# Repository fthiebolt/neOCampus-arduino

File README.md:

# neOCampus-arduino | home of the neOSensor end-devices #
________________________________________________________________
# WE MOVED #
# to https://gitlab.irit.fr/gis-neocampus/neosensor/neOCampus-arduino #
________________________________________________________________

This repository provides support for the following neOCampus boards:
  * neOSensor boards based on ESP32
  * neOSensor-AirQuality board (ESP32) from CNRS' LCC lab.
  * neOSensor boards based on ESP8266 (rev. >= V2)

All this work was undertaken at Université Toulouse 3 / IRIT laboratory in the context of the [neOCampus](https://neocampus.org "neOCampus corporate") operation.

## neOSensor boards ##
neOSensor first boards releases were based on esp8266. Nowadays, we added support for esp32 and CubeCell devices :)

We added support to our neOCampus IoT management infrastructure named [sensOCampus](https://neocampus.univ-tlse3.fr "neOCampus's Wiki Home") to enable a central configuration for all of our neOSensor boards; these boards will then be able to publish their data to our infrastructure and to have those data stored in our databases.

### neOSensor-AirQuality board ###
This board comes from CNRS LCC lab, it's a PhD work undertaken by Aymen Sendi (aymen.sendi@laas.fr).
The board features four specific sensors able to measure NO2, CO, CH20, NO2 alternate.

## Getting started ##
First of all, you ought to install esp32, esp8266 or CubeCell support in your Arduino IDE (IDE version <2).

| Device   | Release   | Arduino Board Manager json file                                                                            |
|----------|-----------|------------------------------------------------------------------------------------------------------------|
| esp8266  | 3.1.2     | https://arduino.esp8266.com/stable/package_esp8266com_index.json                                           |
| esp32    | 2.0.11    | https://raw.githubusercontent.com/espressif/arduino-esp32/gh-pages/package_esp32_index.json                |
| CubeCell | *latest*  | https://github.com/HelTecAutomation/CubeCell-Arduino/releases/download/V1.3.0/package_CubeCell_index.json  |
| stm32    | *latest*  | https://github.com/stm32duino/BoardManagerFiles/raw/main/package_stmicroelectronics_index.json             |

Then, run script `./deploy.sh` and boards will get added to your Arduino boards list :)

If not already installed, you'll need python-serial package; thus either you install it at the system level
```
[fedora] dnf -y install python3-pyserial
[ubuntu] apt-get -y install python3-serial python-is-python3
```

Once you've launched the Arduino IDE, before compiling and uploading sketches to your board, you need to undertake the following steps:
  - @preferences --> set your Arduino sketchbook to `~/neOCampus-arduino/neosensor' ... this will lead to proper libraries
  - either select boards 'ESP32 arduino' --> 'neOSensor' or 'neOSensor-AirQuality' or select board 'ESP8266 arduino' --> 'neOSensor'
  - compile and upload :)
  - debug serial link speed 115200

### WiFi setup ###
Only for ESP based boards.

Once started, the board will provides a WiFi Access Point (AP) named: `neOSensor_xxxx` where xxxx are the MAC address last bytes.

**First time setup**\
In this case, AP will get available for 5mn for you to configure SSID along with WPA2 key.
So you'll have to search with your smartphone for this peucliar AP, and then connect. In case automatic redirection does not work, open a browser with http:192.168.4.1

**Changing WiFi setup**\
Once WiFi has been set, on each reboot, the neOSensor AP will get available for 50s in order for you to tweak some parameters ... or to change the WiFi it connects to.

**Reset whole configuration**\
To erase all of the previously set parameters (including WiFi settings), press the RST button for 10s when powering the device.

***

## Create branch | development of a new feature ##
In order to work on a new feature, best is to create a new branch that will get merged later during a *pull request*

```
git switch -C feature-xxxxx
```

For first commit:
```
git push --set-upstream origin feature-xxxxx
```

... then `./git-push.sh` on subsequent commits

## Merge branch | integration of an existing feature ##
After having successfully completed yout feature, you need to create a *pull request* to get your code integrated into the main branch:

```
git branch
git checkout master
git merge feature-xxxxx
./git-push.sh
```
https://www.w3schools.com/git/git_branch_merge.asp?remote=github

In the end, you can delete your local branch: `git branch -d feature-xxxxx`

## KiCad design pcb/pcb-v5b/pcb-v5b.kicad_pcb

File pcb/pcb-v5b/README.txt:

This directory holds the following:

- pcb-v5b.pro	--> main neOSensor board (esp32 30 pins based version) version 5B

- panelization files (4 designs in a single 100x100mm board)

To launch Kicad: #> kicad xxx.pro

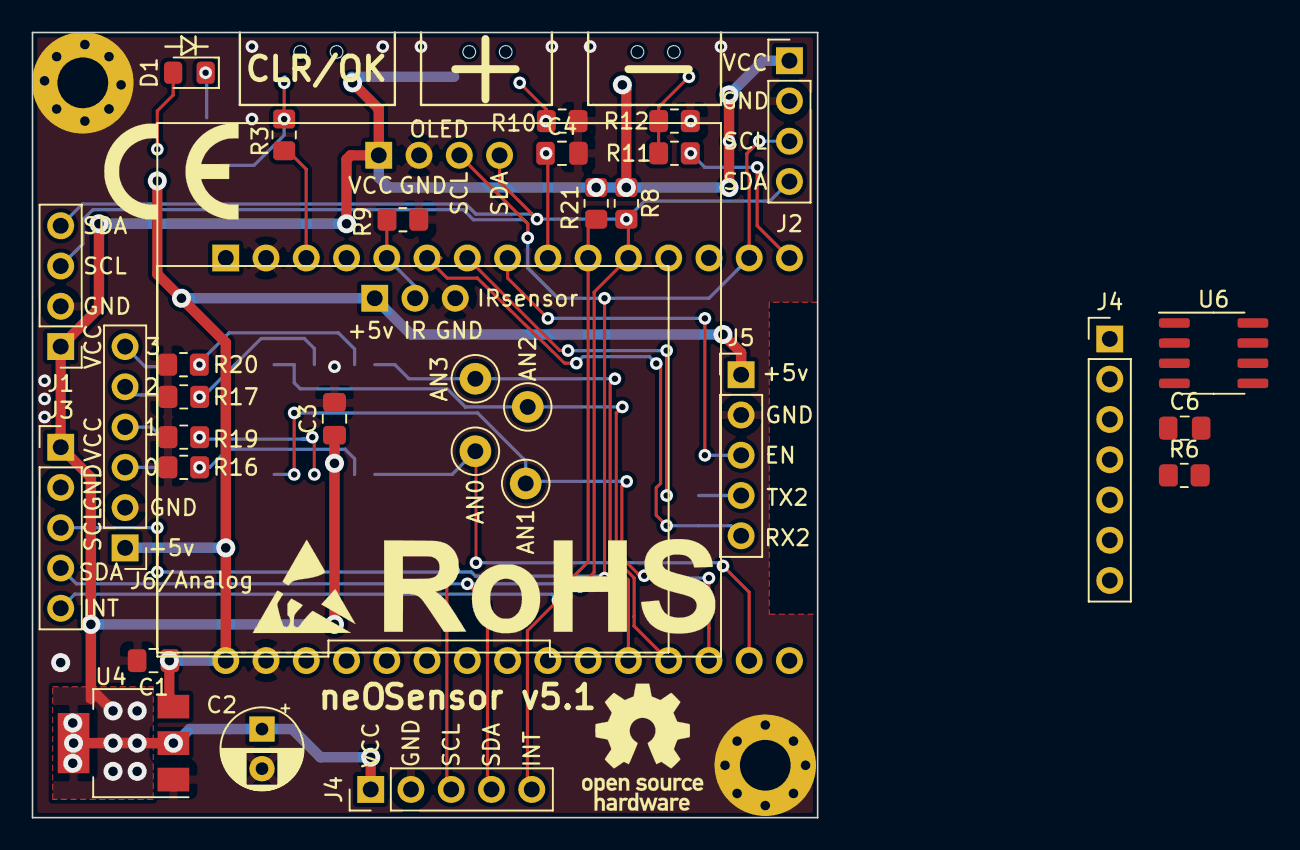
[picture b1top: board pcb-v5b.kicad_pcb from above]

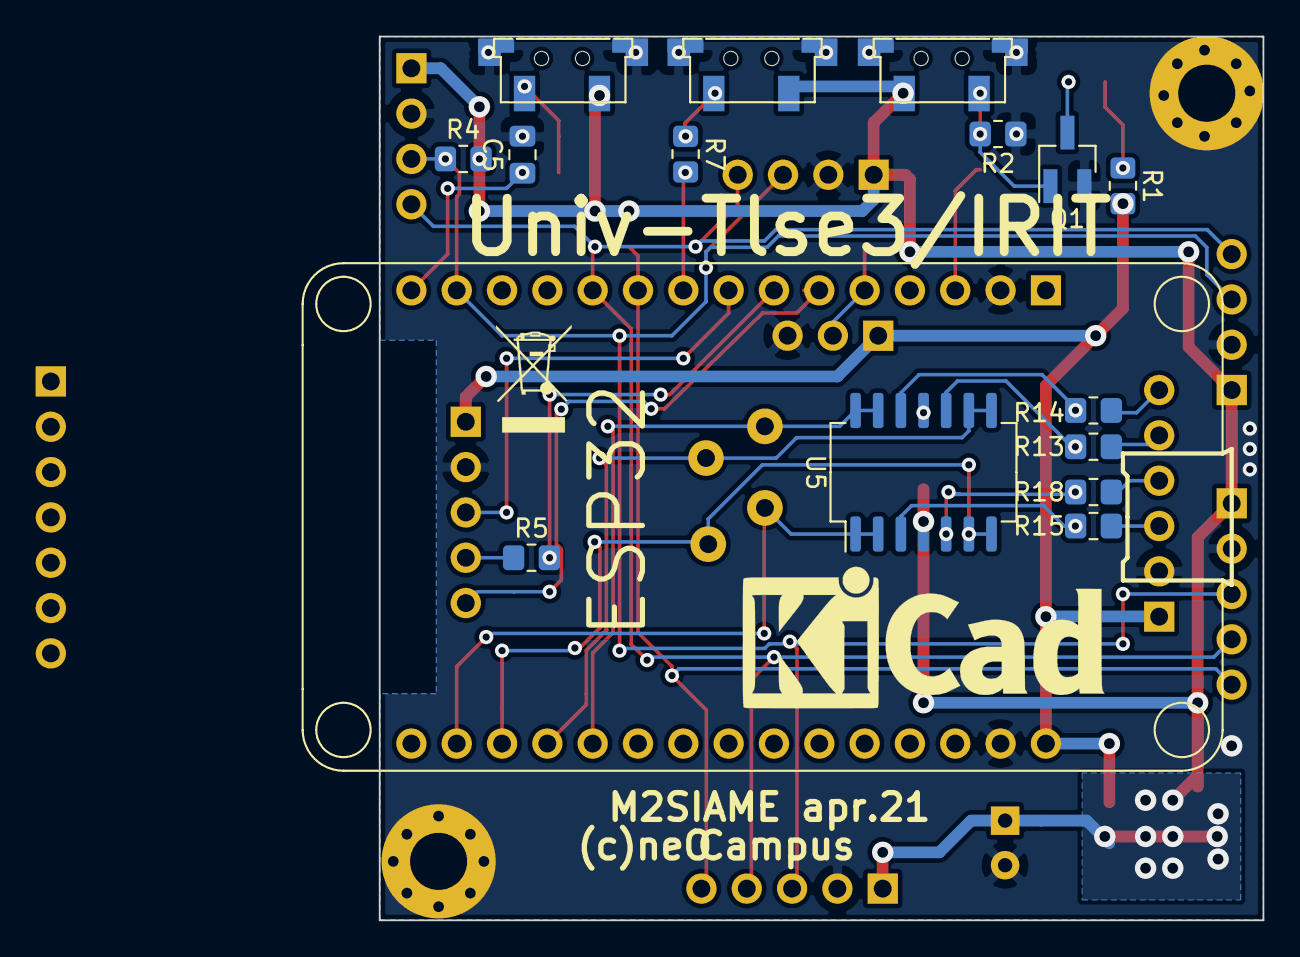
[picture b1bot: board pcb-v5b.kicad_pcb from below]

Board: 2 copper layers, 49.5 x 49.5 mm, 51 parts (16 on the bottom side), 33 nets.

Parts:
C1, C3: 100nF; C_0805_2012Metric_Pad1.18x1.45mm_HandSolder
C2: 100µF 6.3v; CP_Radial_D5.0mm_P2.50mm
C4, C5: 1uF; C_0805_2012Metric_Pad1.18x1.45mm_HandSolder
C6: 100n; C_0805_2012Metric_Pad1.18x1.45mm_HandSolder
D1: Red; LED_0805_2012Metric_Pad1.15x1.40mm_HandSolder
H1, H2: 3.2mm for MH3 screw; MountingHole_3.2mm_M3_Pad
J1, J2: Conn_01x04; PinHeader_1x04_P2.54mm_Vertical
J3, J4, J5: Conn_01x05; PinHeader_1x05_P2.54mm_Vertical
J4#2: Conn_01x07; PinHeader_1x07_P2.54mm_Vertical
J6: Conn_01x06; PinHeader_1x06_P2.54mm_Vertical
Q1: 2N7002; SOT-23_Handsoldering
R1: 150; R_0805_2012Metric_Pad1.20x1.40mm_HandSolder
R2, R7, R9, R10, R11, R12, R21: 15k; R_0805_2012Metric_Pad1.20x1.40mm_HandSolder
R3, R5, R6: 470; R_0805_2012Metric_Pad1.20x1.40mm_HandSolder
R4, R8: 4K7; R_0805_2012Metric_Pad1.20x1.40mm_HandSolder
R13, R14, R15, R18: 22k; R_0805_2012Metric_Pad1.20x1.40mm_HandSolder
R16, R17, R19, R20: 33k; R_0805_2012Metric_Pad1.20x1.40mm_HandSolder
SW1: clear; G71Y_µsw_smd
SW2: +; G71Y_µsw_smd
SW3: -; G71Y_µsw_smd
TP3: tp_an1; TestPoint_Loop_D2.50mm_Drill1.0mm
TP4: tp_an0; TestPoint_Loop_D2.50mm_Drill1.0mm
TP5: tp_an2; TestPoint_Loop_D2.50mm_Drill1.0mm
TP6: tp_an3; TestPoint_Loop_D2.50mm_Drill1.0mm
U1: HC-SR01; PIR_HC-SR01
U2: OLED1.3_I2C
U3: ESP32_dev_30p
U4: AMS1117-3.3; SOT-223-3_TabPin2
U5: LM2902; SO-14_5.3x10.2mm_P1.27mm
U6: ATECC608A-SSHDA; SOIC-8_3.9x4.9mm_P1.27mm

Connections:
+3V3: C2.1, C3.1, J1.1, J2.1, J3.1, J4.1, J4#2.3, R4.2, R8.2, R21.2, SW1.1, SW2.2, SW3.2, U2.1 (VCC), U4.2 (VO), U5.4 (V+), U6.8 (VCC)
+5V: C1.1, J5.1, J6.1, R1.2, U1.1 (V+), U3.30 (VIN), U4.3 (VI)
/ADC1_0: TP4.1, U3.17 (GPIO36), U5.1, U5.2 (-)
/ADC1_3: TP3.1, U3.18 (GPIO39), U5.6 (-), U5.7
/ADC1_6: TP5.1, U3.19 (GPIO34), U5.8, U5.9 (-)
/ADC1_7: TP6.1, U3.20 (GPIO35), U5.13 (-), U5.14
/ANA_0: J6.3, R15.1
/ANA_1: J6.4, R18.1
/ANA_2: J6.5, R13.1
/ANA_3: J6.6, R14.1
/INT: J3.5, J4.5, J4#2.7, R21.1, U3.10 (GPIO19)
/IR: R6.1, R9.2, U1.2 (OUT)
/LED: R3.1, U3.3 (GPIO15)
/PM_EN: J5.3, U3.8 (GPIO5)
/RX2: J5.5, U3.6 (GPIO16)
/SCL: J1.3, J2.3, J3.3, J4.3, J4#2.2, J4#2.5, R4.1, U2.3 (SCL), U3.14 (SCL), U6.6 (SCL)
/SDA: J1.4, J2.4, J3.4, J4.4, J4#2.1, J4#2.6, R8.1, U2.4 (SDA), U3.11 (SDA), U6.5 (SDA)
/SW2: C4.1, R7.2, U3.9 (GPIO18)
/SW3: C5.1, R11.2, U3.15 (GPIO23)
/TX2: J5.4, R5.1
GND: C1.2, C2.2, C3.2, C4.2, C5.2, C6.1, H1.1, H2.1, J1.2, J2.2, J3.2, J4.2, J4#2.4, J5.2, J6.2, Q1.2 (S), R2.1, R9.1, R10.1, R12.1, R16.1, R17.1, R19.1, R20.1, SW1.3, SW2.3, SW3.3, U1.3 (GND), U2.2 (GND), U3.2 (GND), U3.29 (GND), U4.1 (GND), U5.11 (V-), U6.4 (GND)
unnamed: D1.2 (A), R1.1
unnamed: D1.1 (K), Q1.3 (D)
unnamed: Q1.1 (G), R2.2, R3.2, SW1.2
unnamed: R7.1, R10.2, SW2.1
unnamed: R11.1, R12.2, SW3.1
unnamed: C6.2, U3.16 (EN)
unnamed: R6.2, U3.5 (GPIO4)
unnamed: R5.2, U3.7 (GPIO17)
unnamed: R15.2, R16.2, U5.3 (+)
unnamed: R18.2, R19.2, U5.5 (+)
unnamed: R13.2, R17.2, U5.10 (+)
unnamed: R14.2, R20.2, U5.12 (+)

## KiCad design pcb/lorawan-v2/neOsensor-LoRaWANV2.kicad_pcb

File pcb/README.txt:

This directory holds several Kicad5 pcbs:

- pcbv4.pro         --> main neOSensor board (esp8266 version)
- pcbv4-temp.pro    --> addon board featuring a temperature sensor
- neOSensorV4_panel --> neOSensors panelized ;)

Note: we get inspiration from Arduino MKR1300 schematic for power supply

To launch Kicad: #> kicad xxx.pro

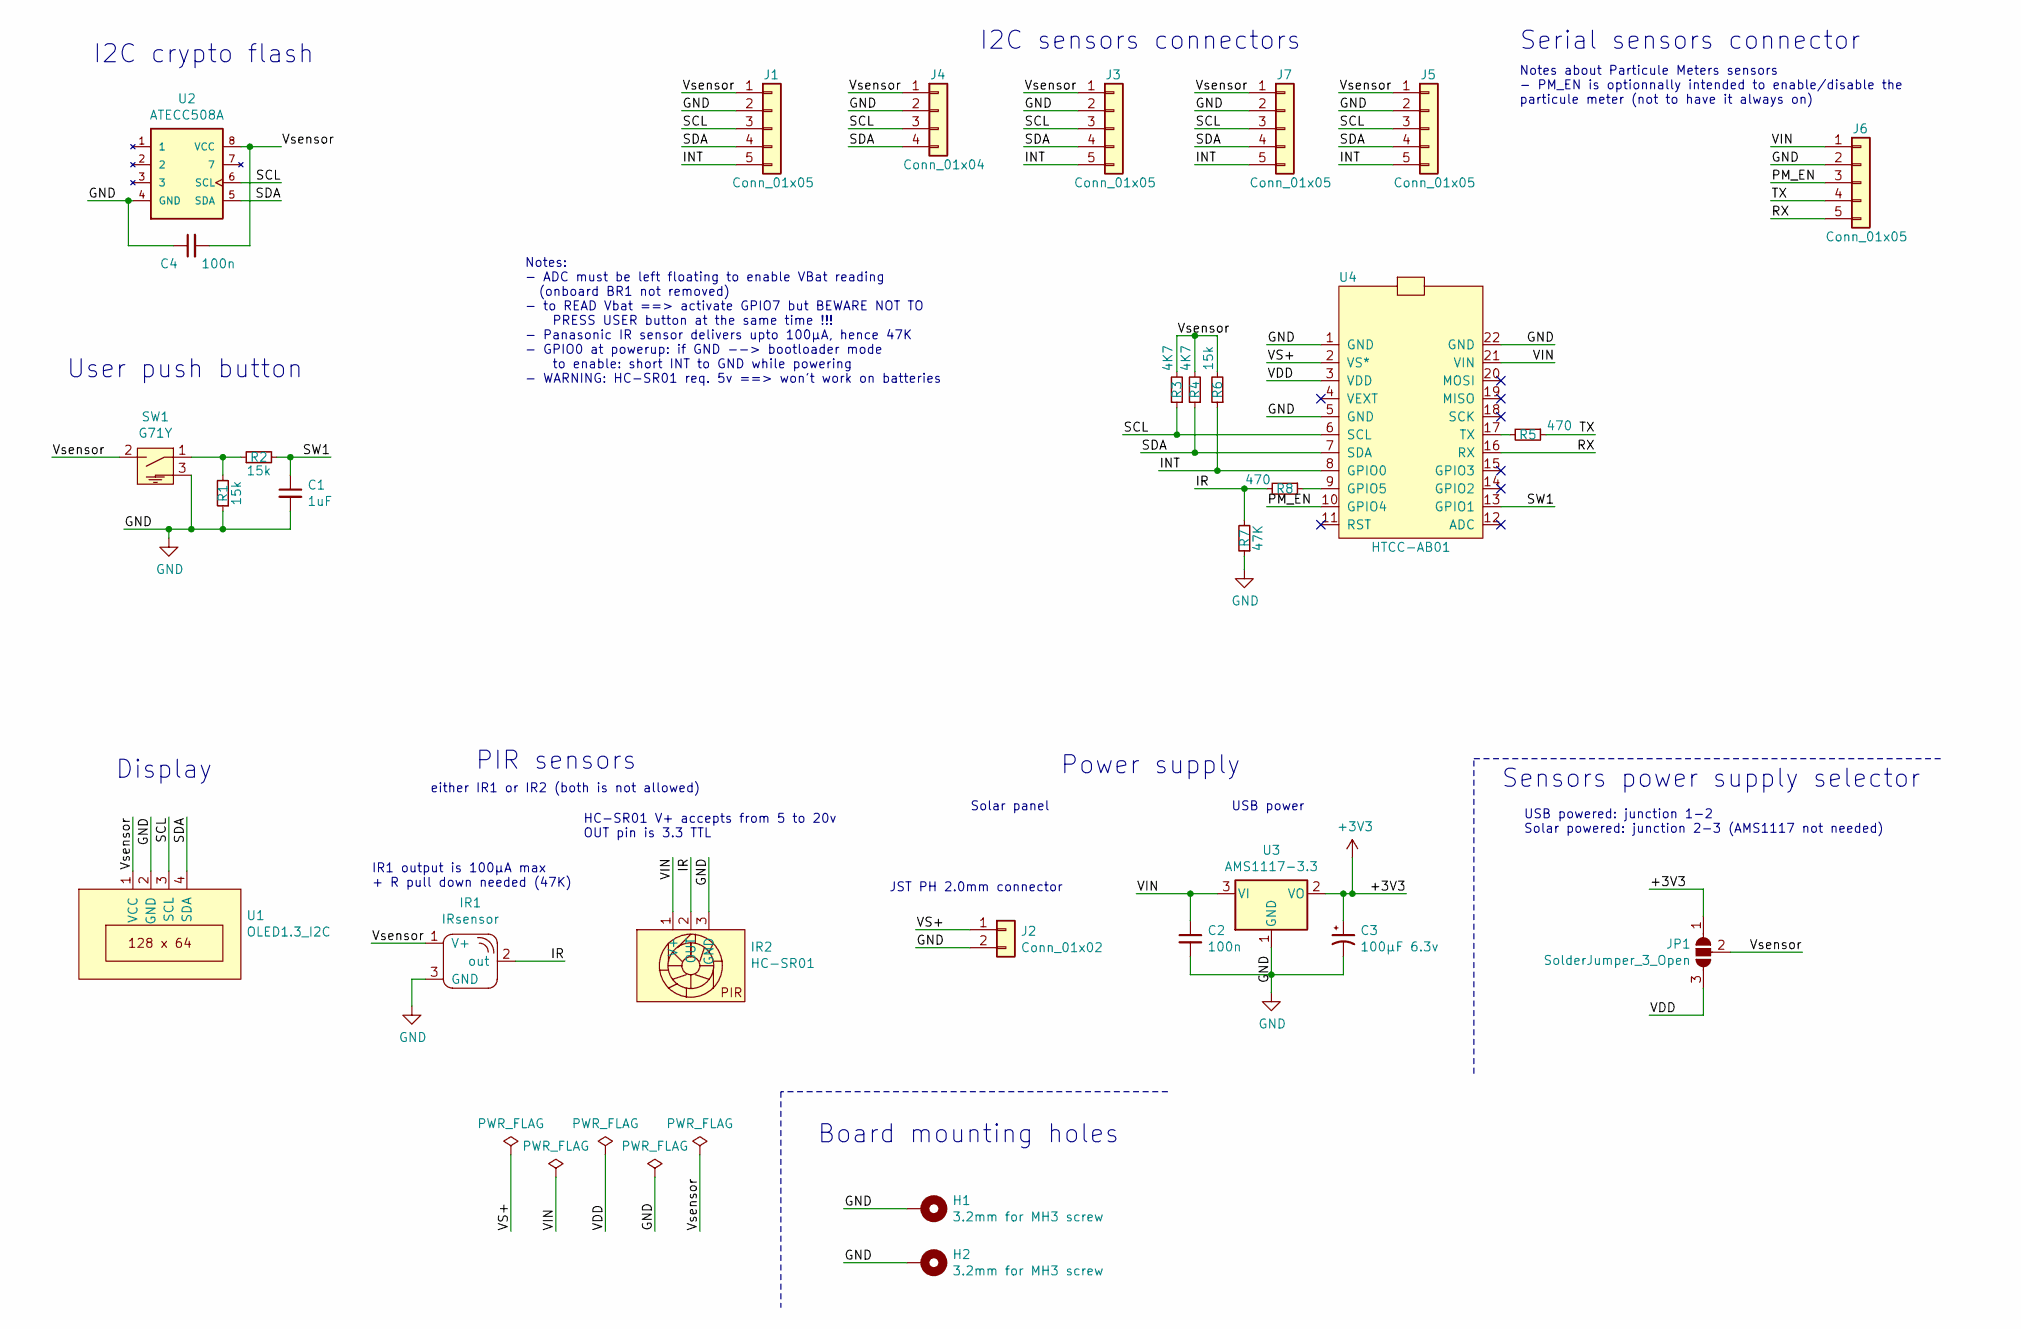
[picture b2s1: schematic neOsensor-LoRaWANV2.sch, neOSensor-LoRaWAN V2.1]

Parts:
C1: 1uF; C_0805_2012Metric_Pad1.15x1.40mm_HandSolder
C2: 100n; C_0805_2012Metric_Pad1.15x1.40mm_HandSolder
C3: 100µF 6.3v; CP_Radial_D5.0mm_P2.50mm
C4: 100n; C_0805_2012Metric_Pad1.18x1.45mm_HandSolder
H1, H2: 3.2mm for MH3 screw; MountingHole_3.2mm_M3_Pad
IR1: IRsensor; IRsensor_TH_and_smd
IR2: HC-SR01; PIR_HC-SR01
J1, J3, J5, J6, J7: Conn_01x05; PinHeader_1x05_P2.54mm_Vertical
J2: Conn_01x02; JST_PH_S2B-PH-K_1x02_P2.00mm_Horizontal
J4: Conn_01x04; PinHeader_1x04_P2.54mm_Vertical
JP1: SolderJumper_3_Open; SolderJumper-3_P1.3mm_Open_RoundedPad1.0x1.5mm
R1, R2, R6: 15k; R_0805_2012Metric_Pad1.15x1.40mm_HandSolder
R3, R4: 4K7; R_0805_2012Metric_Pad1.15x1.40mm_HandSolder
R5, R8: 470; R_0805_2012Metric_Pad1.15x1.40mm_HandSolder
R7: 47K; R_0805_2012Metric_Pad1.15x1.40mm_HandSolder
SW1: G71Y; G71Y_µsw_smd
U1: OLED1.3_I2C
U2: ATECC508A; SOIC-8_3.9x5.4mm_P1.27mm_HandSolder
U3: AMS1117-3.3; SOT-223-3_TabPin2
U4: HTCC-AB01

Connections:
+3V3: C3.1, JP1.1 (A), U3.2 (VO)
/INT: J1.5, J3.5, J5.5, J7.5, R6.1, U4.8 (GPIO0)
/IR: IR1.2 (out), IR2.2 (OUT), R7.2, R8.2
/PM_EN: J6.3, U4.10 (GPIO4)
/RX: J6.5, U4.16 (RX)
/SCL: J1.3, J3.3, J4.3, J5.3, J7.3, R3.1, U1.3 (SCL), U2.6 (SCL), U4.6 (SCL)
/SDA: J1.4, J3.4, J4.4, J5.4, J7.4, R4.1, U1.4 (SDA), U2.5 (SDA), U4.7 (SDA)
/SW1: C1.1, R2.2, U4.13 (GPIO1)
/TX: J6.4, R5.1
/VDD: JP1.3 (B), U4.3 (VDD)
/VIN: C2.1, IR2.1 (V+), J6.1, U3.3 (VI), U4.21 (VIN)
/VS+: J2.1, U4.2 (VS*)
/Vsensor: C4.2, IR1.1 (V+), J1.1, J3.1, J4.1, J5.1, J7.1, JP1.2 (C), R3.2, R4.2, R6.2, SW1.2, U1.1 (VCC), U2.8 (VCC)
GND: C1.2, C2.2, C3.2, C4.1, H1.1, H2.1, IR1.3 (GND), IR2.3 (GND), J1.2, J2.2, J3.2, J4.2, J5.2, J6.2, J7.2, R1.1, R7.1, SW1.3, U1.2 (GND), U2.4 (GND), U3.1 (GND), U4.1 (GND), U4.5 (GND), U4.22 (GND)
unnamed: R1.2, R2.1, SW1.1
unnamed: R5.2, U4.17 (TX)
unnamed: R8.1, U4.9 (GPIO5)

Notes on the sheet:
User push button
I2C crypto flash
I2C sensors connectors
Serial sensors connector
Board mounting holes
Display
Power supply
Notes: - ADC must be left floating to enable VBat reading (onboard BR1 not removed) - to READ Vbat ==> activate GPIO7 but BEWARE NOT TO PRESS USER button at the same time !!! - Panasonic IR sensor delivers upto 100µA, hence 47K - GPIO0 at powerup: if GND --> bootloader mode to enable: short INT to 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
Notes about Particule Meters sensors - PM_EN is optionnally intended to enable/disable the particule meter (not to have it always on)
PIR sensors
HC-SR01 V+ accepts from 5 to 20v OUT pin is 3.3 TTL
either IR1 or IR2 (both is not allowed)
IR1 output is 100µA max + R pull down needed (47K)
Sensors power supply selector
USB powered: junction 1-2 Solar powered: junction 2-3 (AMS1117 not needed)
USB power
Solar panel
JST PH 2.0mm connector

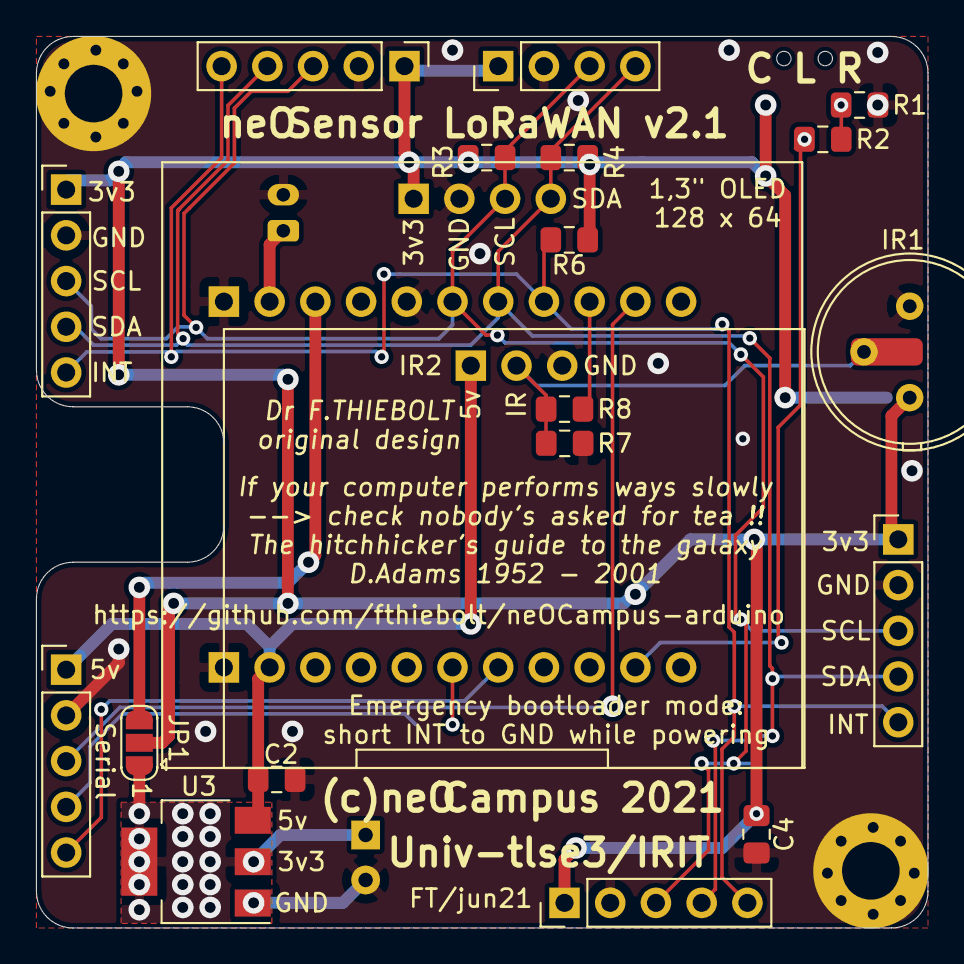
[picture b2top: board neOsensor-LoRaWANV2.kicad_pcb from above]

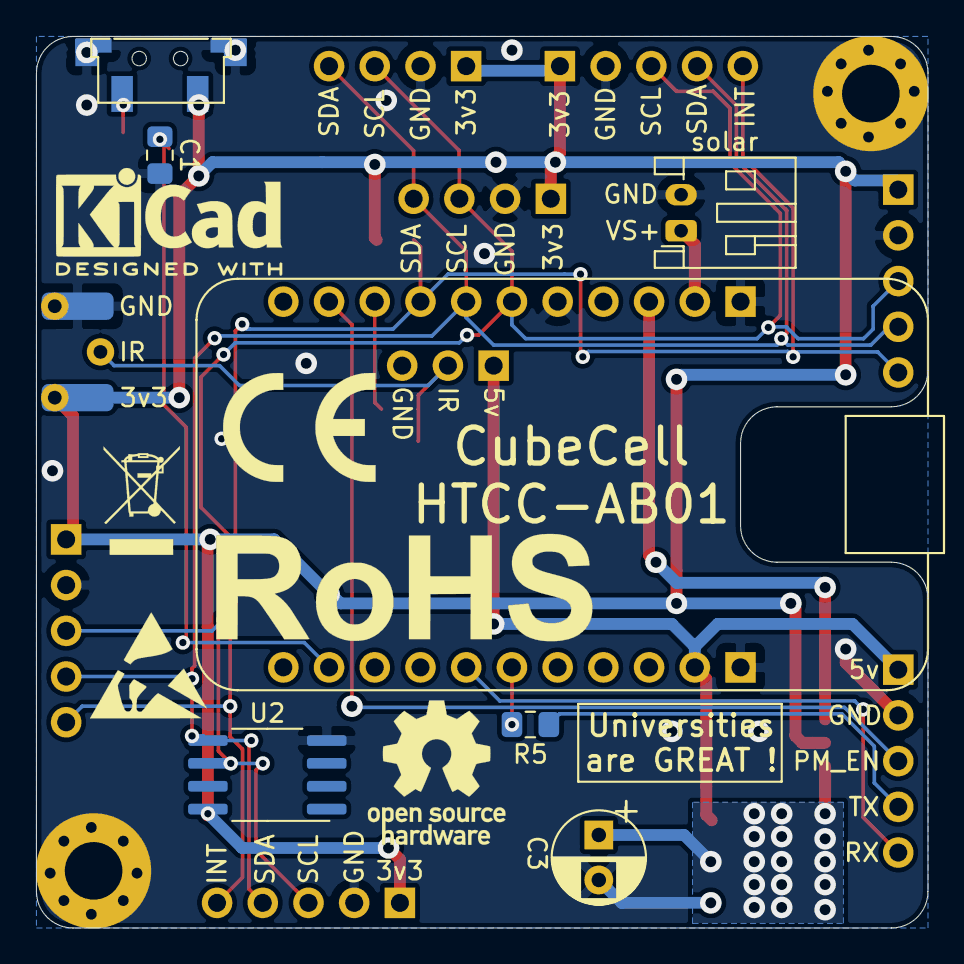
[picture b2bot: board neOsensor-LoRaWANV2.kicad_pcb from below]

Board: 2 copper layers, 49.5 x 49.5 mm, 29 parts (7 on the bottom side), 17 nets.

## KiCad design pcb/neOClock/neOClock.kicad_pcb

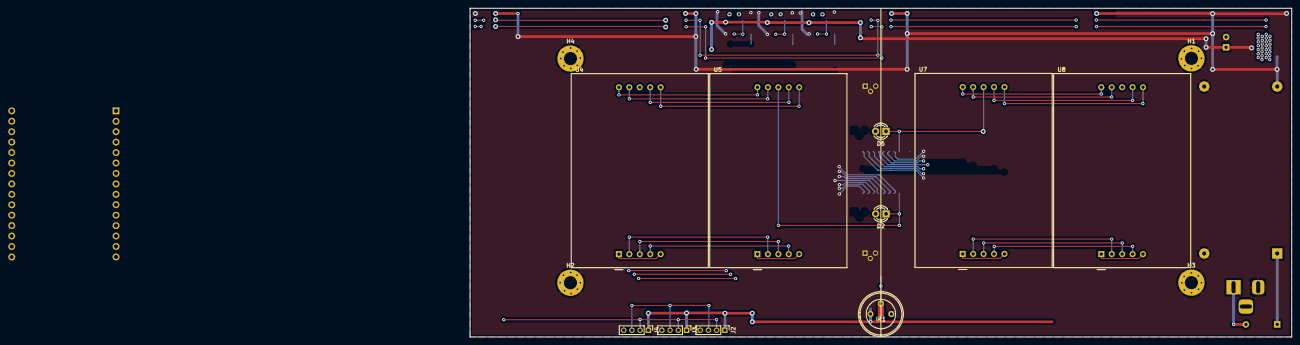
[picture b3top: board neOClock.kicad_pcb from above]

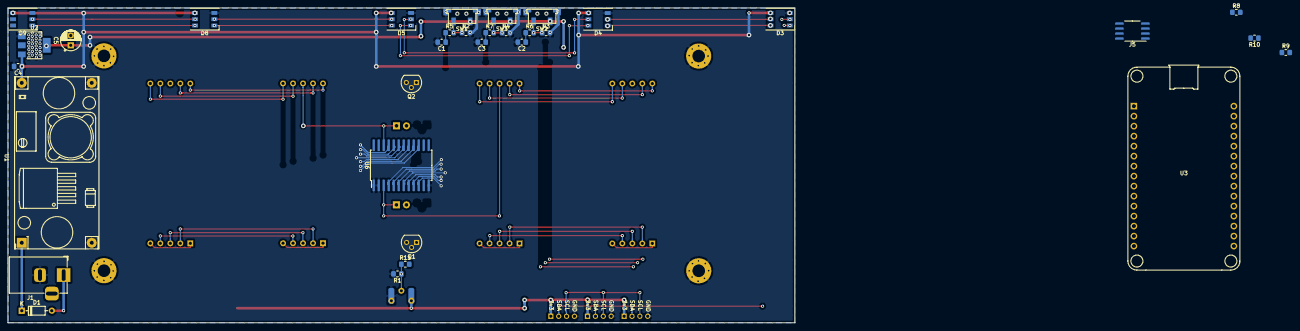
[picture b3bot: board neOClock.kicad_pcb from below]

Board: 2 copper layers, 200.0 x 80.0 mm, 47 parts (33 on the bottom side), 46 nets.

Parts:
C1, C2, C3: 1µF; R_0805_2012Metric_Pad1.20x1.40mm_HandSolder
C4: 100nF; R_0805_2012Metric_Pad1.20x1.40mm_HandSolder
C5: 100µF; CP_Radial_D5.0mm_P2.50mm
D1: 1N4148; D_DO-35_SOD27_P7.62mm_Horizontal
D2, D6: LED; LED_D3.0mm
D3, D4, D5, D8, D9: APA102; LED_WS2812_PLCC6_5.0x5.0mm_P1.6mm
H1, H2, H3, H4: MountingHole_Pad; MountingHole_3.2mm_M3_Pad
IR1: IRsensor; IRsensor_TH_and_smd
J1: Barrel_Jack; BarrelJack_Horizontal
J2, J3, J4: Conn_01x04; PinHeader_1x04_P2.00mm_Vertical
J5: ATECC508A; SOIC-8_3.9x5.4mm_P1.27mm_HandSolder
Q1, Q2: 2n2222a; TO-92
R1: 47k; R_0805_2012Metric_Pad1.20x1.40mm_HandSolder
R2, R3, R4, R5, R6, R7: 15K; R_0805_2012Metric_Pad1.20x1.40mm_HandSolder
R8, R9: 4.7K; R_0805_2012Metric_Pad1.20x1.40mm_HandSolder
R10, R11: 470; R_0805_2012Metric_Pad1.20x1.40mm_HandSolder
SW1, SW2, SW3: G71Y; G71Y_µsw_smd
U1: DCDC_LM2596; DC_DC_LM2596
U2: AMS1117; SOT-223-3_TabPin2
U3: ESP32_dev_30p
U4, U5, U7, U8: SA15-11GWA; SA15-11xxx
U6: SAA1064; SOIC-24W_7.5x15.4mm_P1.27mm_HandSolder

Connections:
0: C1.2, C2.2, C3.2, C4.2, C5.2, D3.3, D4.3, D5.3, D8.3, D9.3, H1.1, H2.1, H3.1, H4.1, IR1.3, J1.2, J2.4, J3.4, J4.4, J5.4, R1.2, R2.2, R3.2, R4.2, SW1.3, SW2.3, SW3.3, U1.2, U1.3, U2.1, U3.2, U3.29, U6.1, U6.2, U6.12
3v3: C5.1, IR1.1, J2.1, J3.1, J4.1, J5.8, R8.2, R9.2, SW1.2, SW2.2, SW3.2, U2.2
5v: C4.1, D3.4, D4.4, D5.4, D8.4, D9.4, U1.4, U2.3, U3.30
12v: D1.1, Q1.1, Q2.1, U1.1, U6.13
/a1_5: Q1.2, U6.11
/a2: U4.2, U5.2, U6.6
/a3: U4.3, U5.3, U6.7
/a4: U4.4, U5.4, U6.8
/a6: U4.6, U5.6, U6.9
/a7: U4.7, U5.7, U6.10
/a8: D2.1, U5.8, U6.3
/a9: U4.9, U5.9, U6.5
/a10: U4.10, U5.10, U6.4
/b1_5: Q2.2, U6.14
/b2: U6.19, U7.2, U8.2
/b3: U6.18, U7.3, U8.3
/b4: U6.17, U7.4, U8.4
/b6: U6.16, U7.6, U8.6
/b7: U6.15, U7.7, U8.7
/b8: D6.1, U6.22, U7.8
/b9: U6.20, U7.9, U8.9
/b10: U6.21, U7.10, U8.10
CI: D3.2, U3.9
DI: D3.1, U3.15
IR: R11.2, U3.5
unnamed: D1.2, J1.1
unnamed: D2.2, Q1.3, U4.1, U4.5, U7.1, U7.5
unnamed: D3.5, D4.2
unnamed: D3.6, D4.1
unnamed: D4.5, D5.2
unnamed: D4.6, D5.1
unnamed: D5.5, D8.2
unnamed: D5.6, D8.1
unnamed: D6.2, Q2.3, U5.1, U5.5, U8.1, U8.5
unnamed: D8.5, D9.2
unnamed: D8.6, D9.1
unnamed: IR1.2, R1.1, R11.1
unnamed: R2.1, R5.2, SW1.1
unnamed: R3.1, R6.2, SW2.1
unnamed: R4.1, R7.2, SW3.1
unnamed: R10.2, U3.13
Push_1: C1.1, R5.1, U3.17
Push_2: C2.1, R6.1, U3.18
Push_3: C3.1, R7.1, U3.19
SCL: J2.3, J3.3, J4.3, J5.6, R8.1, U3.14, U6.24
SDA: J2.2, J3.2, J4.2, J5.5, R9.1, U3.11, U6.23

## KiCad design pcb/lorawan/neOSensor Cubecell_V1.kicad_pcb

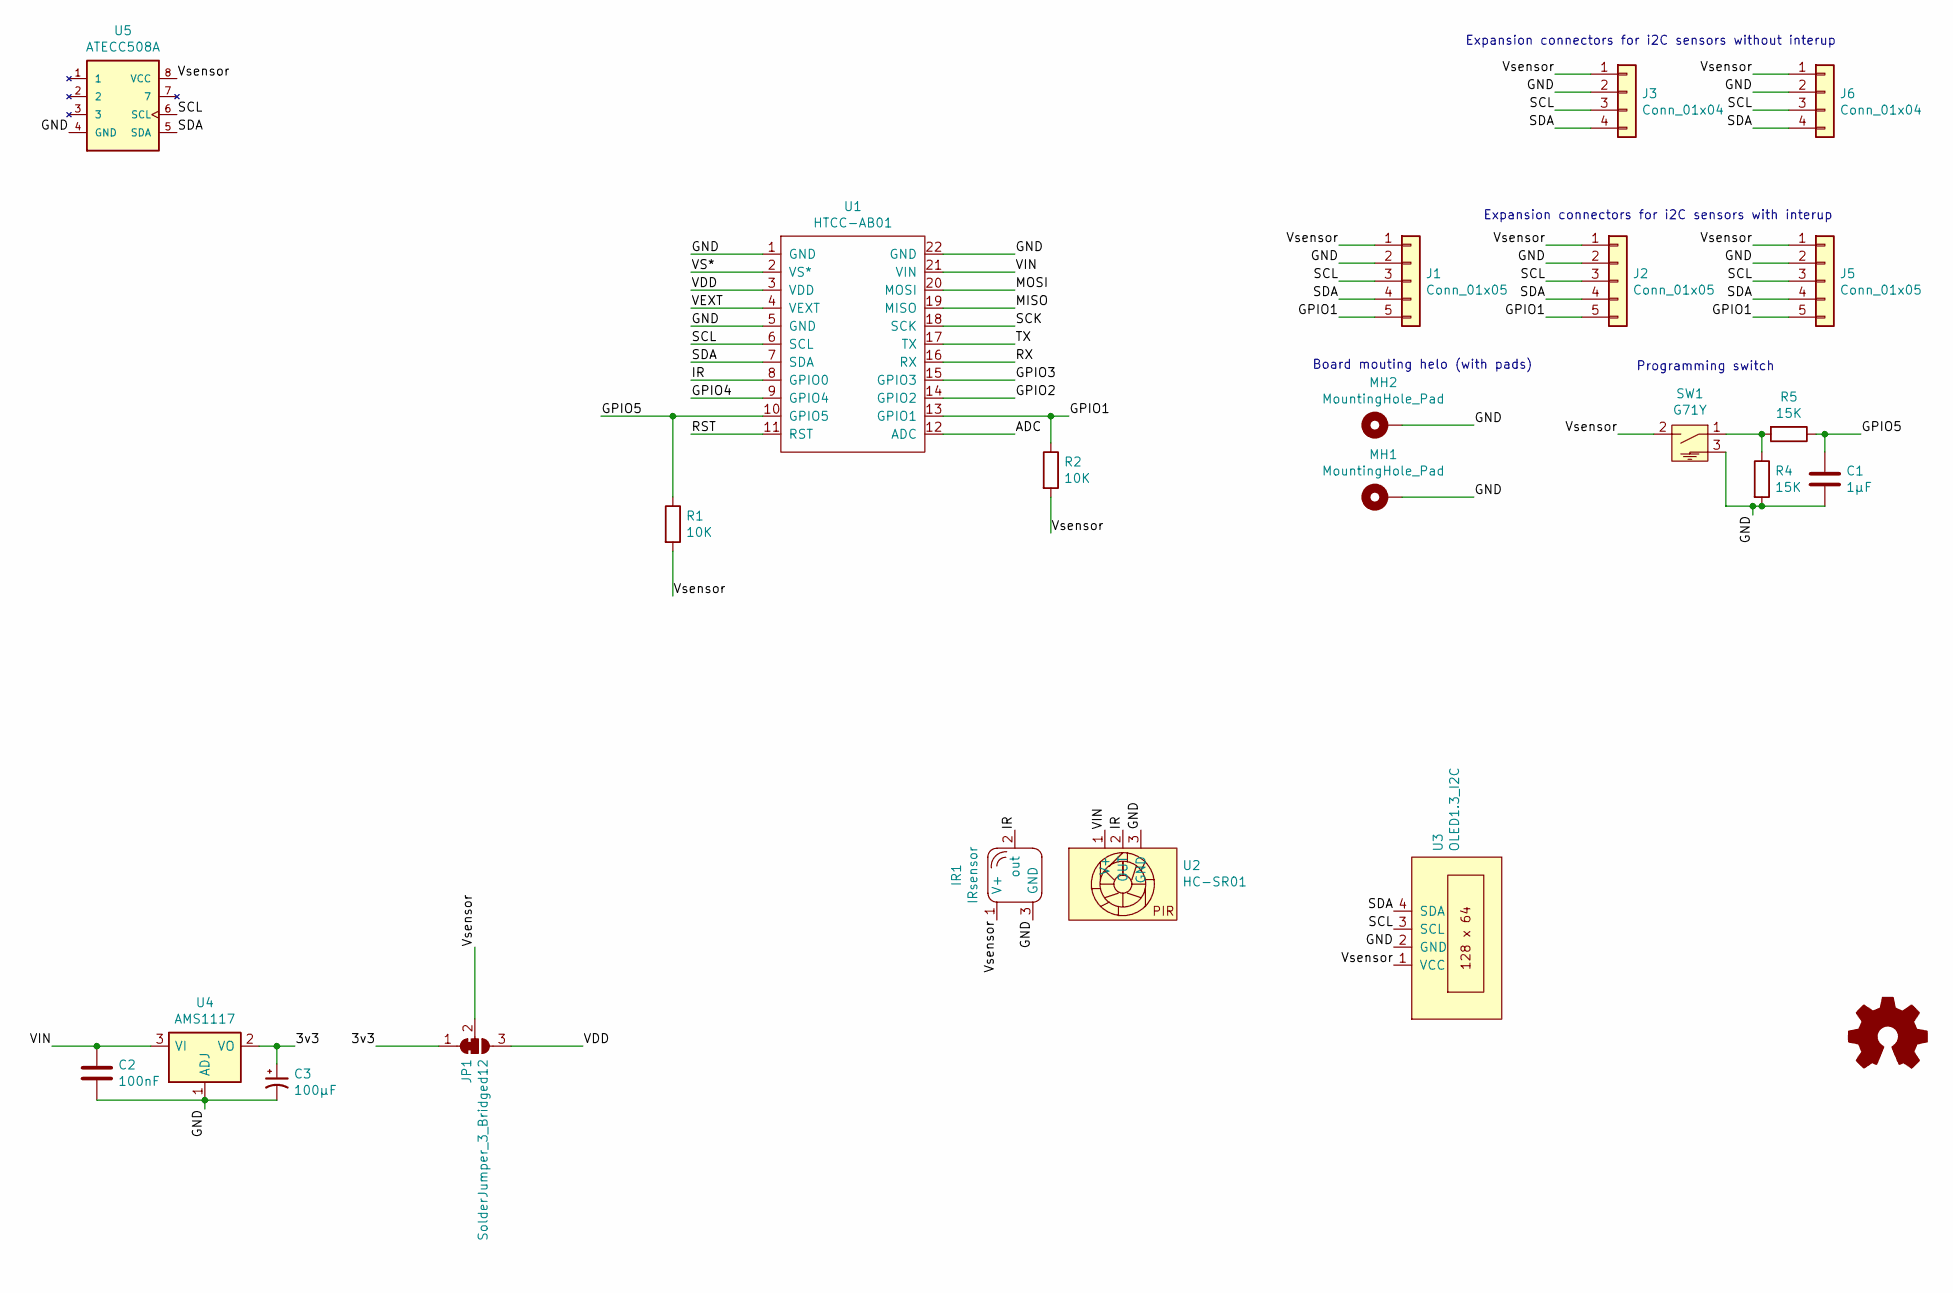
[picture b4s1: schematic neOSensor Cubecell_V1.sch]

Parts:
C1: 1µF; R_0805_2012Metric_Pad1.20x1.40mm_HandSolder
C2: 100nF; C_0805_2012Metric_Pad1.15x1.40mm_HandSolder
C3: 100µF; CP_Radial_D5.0mm_P2.50mm
IR1: IRsensor; IRsensor_TH_and_smd
J1, J2, J5: Conn_01x05; PinHeader_1x05_P2.54mm_Vertical
J3, J6: Conn_01x04; PinHeader_1x04_P2.54mm_Vertical
JP1: SolderJumper_3_Bridged12; SolderJumper-3_P1.3mm_Bridged2Bar12_Pad1.0x1.5mm
MH1, MH2: MountingHole_Pad; MountingHole_3.2mm_M3_Pad
R1, R2: 10K; R_0805_2012Metric_Pad1.15x1.40mm_HandSolder
R4, R5: 15K; R_0805_2012Metric_Pad1.15x1.40mm_HandSolder
SW1: G71Y; G71Y_µsw_smd
U1: HTCC-AB01
U2: HC-SR01; PIR_HC-SR01
U3: OLED1.3_I2C
U4: AMS1117; SOT-223-3_TabPin2
U5: ATECC508A; SOIC-8_3.9x5.4mm_P1.27mm_HandSolder

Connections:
/3v3: C3.1, JP1.1 (A), U4.2 (VO)
/ADC: U1.12 (ADC)
/GND: C1.2, C2.2, C3.2, IR1.3 (GND), J1.2, J2.2, J3.2, J5.2, J6.2, MH1.1, MH2.1, R4.2, SW1.3, U1.1 (GND), U1.5 (GND), U1.22 (GND), U2.3 (GND), U3.2 (GND), U4.1 (ADJ), U5.4 (GND)
/GPIO1: J1.5, J2.5, J5.5, R2.1, U1.13 (GPIO1)
/GPIO2: U1.14 (GPIO2)
/GPIO3: U1.15 (GPIO3)
/GPIO4: U1.9 (GPIO4)
/GPIO5: C1.1, R1.1, R5.1, U1.10 (GPIO5)
/IR: IR1.2 (out), U1.8 (GPIO0), U2.2 (OUT)
/MISO: U1.19 (MISO)
/MOSI: U1.20 (MOSI)
/RST: U1.11 (RST)
/RX: U1.16 (RX)
/SCK: U1.18 (SCK)
/SCL: J1.3, J2.3, J3.3, J5.3, J6.3, U1.6 (SCL), U3.3 (SCL), U5.6 (SCL)
/SDA: J1.4, J2.4, J3.4, J5.4, J6.4, U1.7 (SDA), U3.4 (SDA), U5.5 (SDA)
/TX: U1.17 (TX)
/VDD: JP1.3 (B), U1.3 (VDD)
/VEXT: U1.4 (VEXT)
/VIN: C2.1, U1.21 (VIN), U2.1 (V+), U4.3 (VI)
/VS*: U1.2 (VS*)
/Vsensor: IR1.1 (V+), J1.1, J2.1, J3.1, J5.1, J6.1, JP1.2 (C), R1.2, R2.2, SW1.2, U3.1 (VCC), U5.8 (VCC)
unnamed: R4.1, R5.2, SW1.1

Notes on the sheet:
Expansion connectors for i2C sensors with interup
Programming switch
Board mouting helo (with pads)
Expansion connectors for i2C sensors without interup

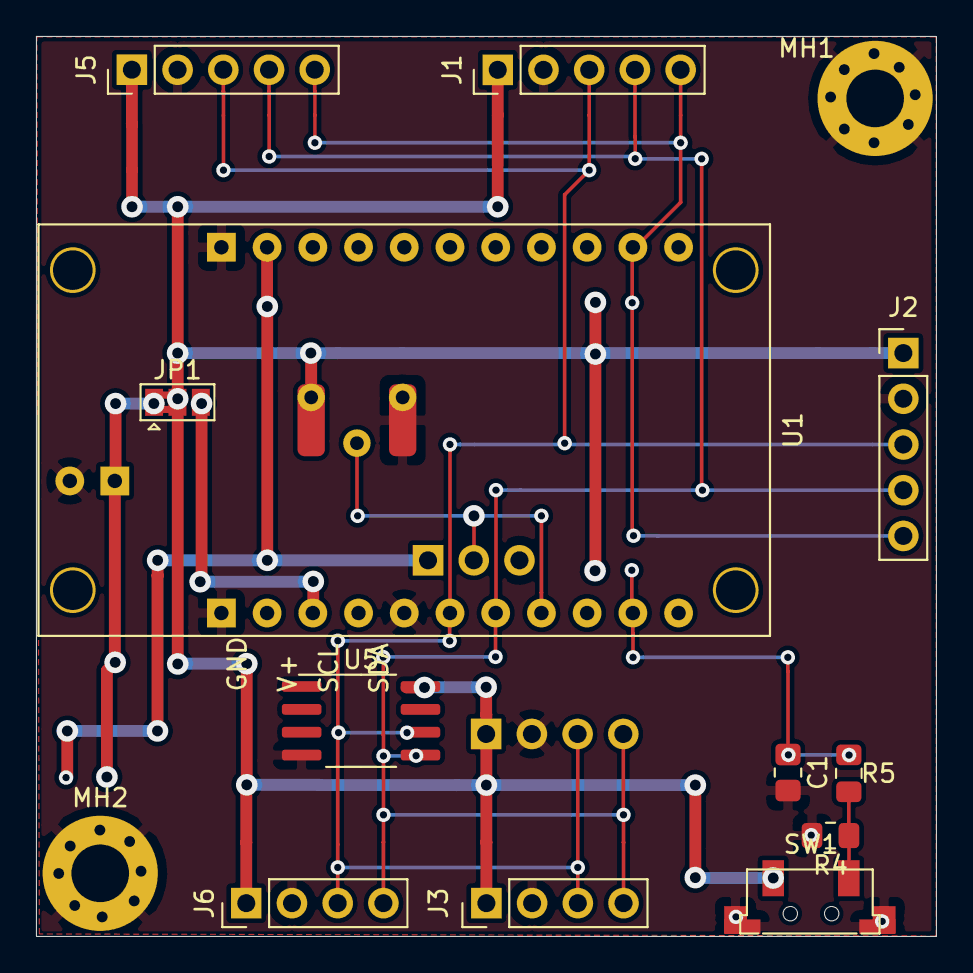
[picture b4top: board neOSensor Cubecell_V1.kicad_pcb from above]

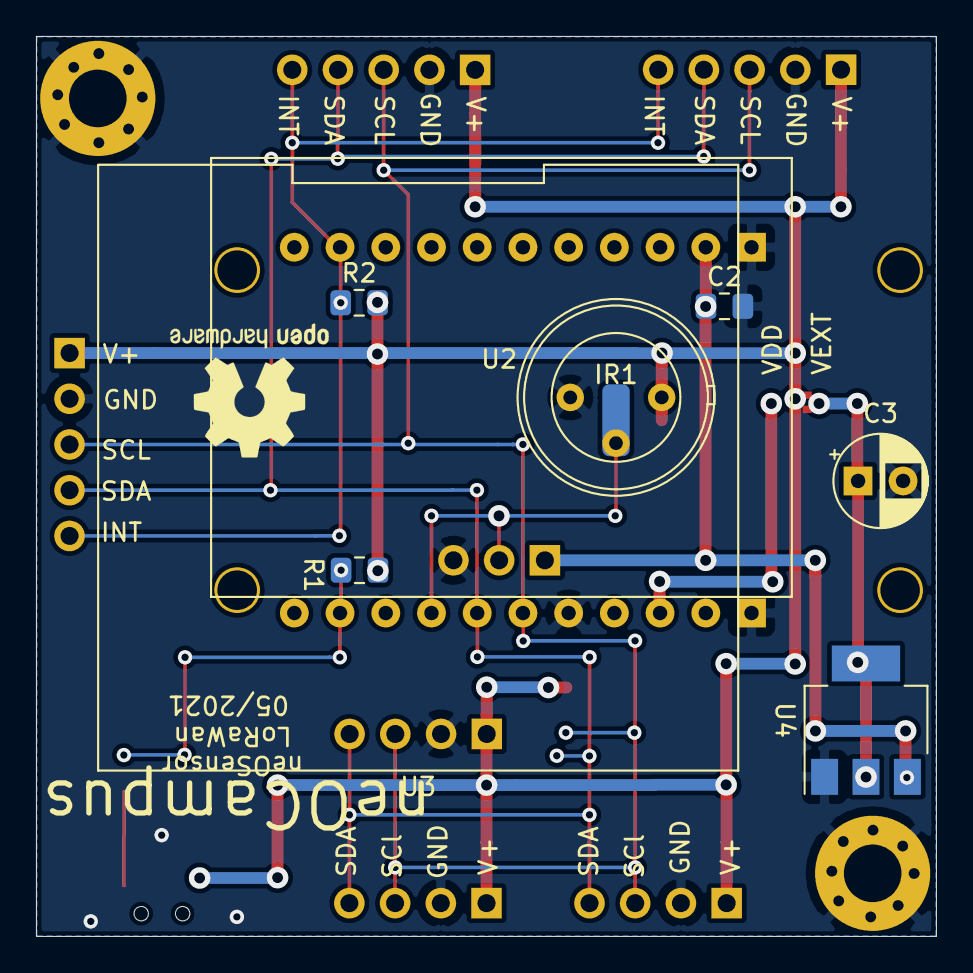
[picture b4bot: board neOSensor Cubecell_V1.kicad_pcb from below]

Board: 2 copper layers, 50.0 x 50.0 mm, 22 parts (8 on the bottom side), 11 nets.
